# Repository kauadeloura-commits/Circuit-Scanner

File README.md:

# Circuit Scanner

Programa de reconhecimento, revisão e simulação de circuitos eletrônicos fotografados. O aplicativo fica em `project/`.

## Executar no Windows

Na pasta `project`, instale as dependências e abra o programa:

```powershell
python -m venv venv
.\venv\Scripts\python.exe -m pip install -r requirements.txt
.\venv\Scripts\python.exe iniciar_scanner.py
```

Os modelos, referências de reconhecimento, dados ativos de aprendizado e circuitos já salvos foram preservados. A versão principal contém os arquivos usados pelo aplicativo, sem relatórios antigos, auditorias, testes ou cópias de desenvolvimento.

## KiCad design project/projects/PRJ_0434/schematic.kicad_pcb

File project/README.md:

# Circuit Scanner — Etapa 5

Esta versão mantém as Etapas 1–4 e adiciona reconhecimento de componentes
com Ultralytics YOLO.

## O que a Etapa 5 acrescenta

- treinamento do detector;
- modelo salvo em `models/circuit_scanner_yolo.pt`;
- status do modelo na interface;
- reconhecimento dentro de cada projeto;
- classe de cada objeto;
- confiança da previsão;
- bounding box;
- `detections.png`;
- `detections.json`;
- persistência do resultado no SQLite.

## Arquivos principais novos

### backend/recognition.py

Carrega o modelo treinado e converte a saída YOLO para o formato usado
pelo Circuit Scanner.

### scripts/train_yolo.py

Treina o modelo usando `dataset/`.

### scripts/validate_yolo.py

Executa validação do modelo final.

### scripts/detect_image.py

Permite testar o modelo em uma imagem avulsa pelo terminal.

### frontend/yolo.html

Mostra se a biblioteca Ultralytics está instalada e se o modelo final existe.

## Instalação

No CMD do VS Code:

    python -m venv venv
    venv\Scripts\activate
    pip install -r requirements.txt

Backend:

    uvicorn backend.main:app --reload

Frontend, em outro terminal:

    python -m http.server 5500 --directory frontend

Site:

    http://127.0.0.1:5500

## Preparar o dataset

A versão ZIP contém apenas uma pequena amostra para conferência de estrutura.

Antes do treino útil, abra:

    http://127.0.0.1:5500/dataset.html

e gere 150 imagens por classe ou mais.

## Treinar

Em um terceiro terminal:

    venv\Scripts\activate
    python scripts\train_yolo.py --epochs 10

Esse é o teste inicial.

Depois:

    python scripts\train_yolo.py --epochs 50

O arquivo esperado é:

    models/circuit_scanner_yolo.pt

O script usa por padrão `yolo26n.pt` como modelo base e salva o melhor peso
do treinamento com o nome usado pelo Circuit Scanner.

## Detectar

Abra um projeto no site e clique:

    Reconhecer componentes com YOLO

O backend usa a imagem original por padrão. A detecção automática executa o
modelo na imagem colorida e também em escala de cinza. Se a imagem colorida
não retornar componentes, é feita ainda uma tentativa em escala de cinza com
resolução maior. Isso evita a perda observada em fotos com iluminação colorida
e no `processed.png` binarizado.

Para testar uma imagem pelo terminal:

    python scripts\detect_image.py caminho\imagem.jpg

Para auditar classes, labels, distribuição dos dados e modelo ativo:

    python scripts\audit_stage5.py

Resultado na pasta do projeto:

    original.png/jpg
    processed.png
    processing.json
    detections.png
    detections.json

As caixas verdes são previsões estáveis. As caixas laranjas com `?` devem ser
conferidas porque possuem confiança baixa ou conflito entre classes parecidas.

Exemplo de `detections.json`:

    {
      "count": 2,
      "detections": [
        {
          "detection_id": "DET_001",
          "class": "resistor",
          "confidence": 0.91,
          "bbox": {
            "x1": 120,
            "y1": 80,
            "x2": 260,
            "y2": 140
          }
        }
      ]
    }

## Observação importante

O ZIP entrega toda a infraestrutura e o código de treinamento/detecção,
mas não contém um modelo Circuit Scanner já treinado. O peso `.pt` depende
do dataset e precisa ser criado executando o treinamento.

Treinar sem erros não é suficiente para concluir a etapa. A conclusão exige
testar cinco circuitos inéditos com a imagem original e registrar componentes
reais, reconhecidos, trocados e ausentes. Falhas pontuais podem ser corrigidas
na conferência; falhas sistemáticas exigem novas anotações reais.

## Ainda não entra nesta etapa

- OCR de R1, 10k, C1 etc.;
- detecção dos terminais;
- fios;
- junções;
- conectividade;
- ngspice;
- KiCad;
- PCB;
- QR Code.

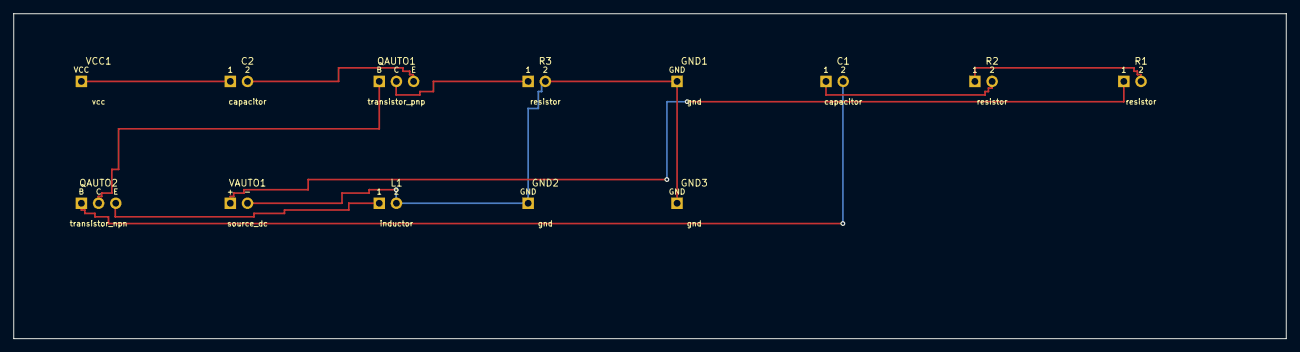
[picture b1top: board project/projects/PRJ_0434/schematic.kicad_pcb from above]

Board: 2 copper layers, 188.0 x 48.0 mm, 13 parts (0 on the bottom side), 10 nets.

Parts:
C1, C2: capacitor; terminal_2
GND1, GND2, GND3: gnd; terminal_1
L1: inductor; terminal_2
QAUTO1: transistor_pnp; terminal_3
QAUTO2: transistor_npn; terminal_3
R1, R2, R3: resistor; terminal_2
VAUTO1: source_dc; terminal_2
VCC1: vcc; terminal_1

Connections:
GND: GND1.1, GND2.1, GND3.1, L1.2, R3.2, VAUTO1.2
NET_1: C2.2, QAUTO1.3
NET_2: QAUTO1.1, QAUTO2.2
NET_5: QAUTO1.2, R3.1
NET_6: R1.2, R2.1
NET_7: C1.1, R2.2
NET_8: C1.2, QAUTO2.1
NET_9: R1.1, VAUTO1.1
NET_13: L1.1, QAUTO2.3
NET_14: C2.1, VCC1.1

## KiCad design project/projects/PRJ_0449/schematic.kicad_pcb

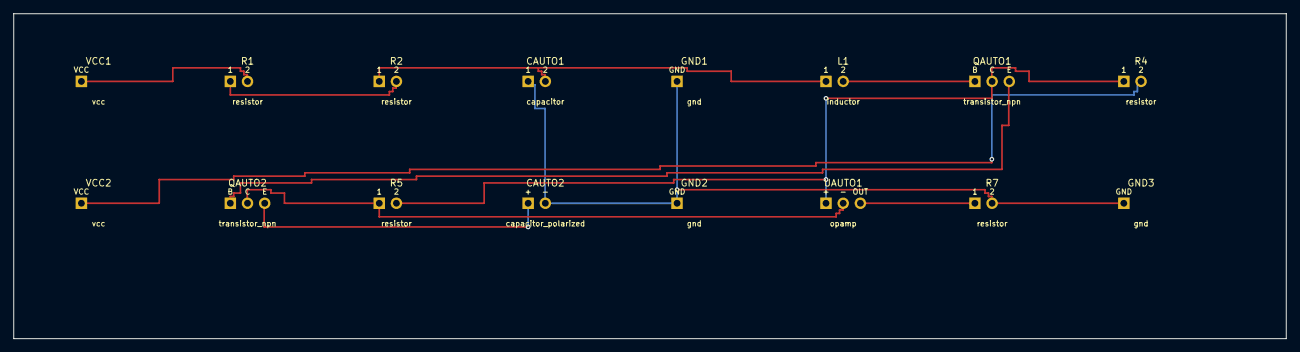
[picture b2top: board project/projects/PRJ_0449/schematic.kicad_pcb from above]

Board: 2 copper layers, 188.0 x 48.0 mm, 16 parts (0 on the bottom side), 11 nets.

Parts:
CAUTO1: capacitor; terminal_2
CAUTO2: capacitor_polarized; terminal_2
GND1, GND2, GND3: gnd; terminal_1
L1: inductor; terminal_2
QAUTO1, QAUTO2: transistor_npn; terminal_3
R1, R2, R4, R5, R7: resistor; terminal_2
UAUTO1: opamp; terminal_3
VCC1, VCC2: vcc; terminal_1

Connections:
GND: CAUTO1.1, CAUTO2.2, GND1.1, GND2.1, GND3.1, R7.2
NET_1: R1.2, VCC1.1
NET_2: R1.1, R2.2
NET_3: CAUTO1.2, L1.1, R2.1
NET_5: L1.2, QAUTO1.1
NET_6: QAUTO1.2, R4.1, R5.2, UAUTO1.1
NET_7: QAUTO1.3, QAUTO2.1
NET_8: R4.2, VCC2.1
NET_9: QAUTO2.2, R5.1, UAUTO1.2
NET_10: CAUTO2.1, QAUTO2.3
NET_11: R7.1, UAUTO1.3

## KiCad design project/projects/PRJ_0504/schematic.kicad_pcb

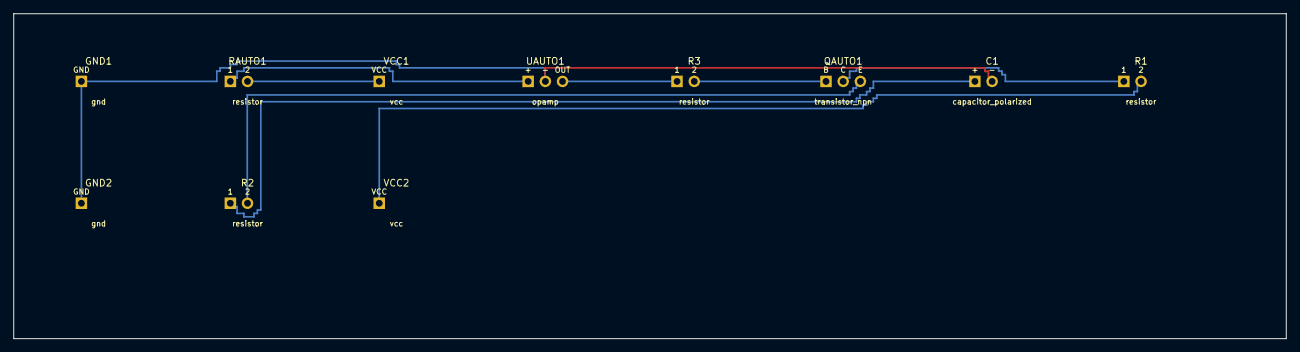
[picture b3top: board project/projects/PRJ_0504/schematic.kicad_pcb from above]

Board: 2 copper layers, 188.0 x 48.0 mm, 11 parts (0 on the bottom side), 9 nets.

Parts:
C1: capacitor_polarized; terminal_2
GND1, GND2: gnd; terminal_1
QAUTO1: transistor_npn; terminal_3
R1, R2, R3: resistor; terminal_2
RAUTO1: resistor; terminal_2
UAUTO1: opamp; terminal_3
VCC1, VCC2: vcc; terminal_1

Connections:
GND: C1.2, GND1.1, GND2.1, UAUTO1.2
NET_2: RAUTO1.1, UAUTO1.1
NET_3: RAUTO1.2, VCC1.1
NET_4: R3.1, UAUTO1.3
NET_5: QAUTO1.1, R3.2
NET_6: QAUTO1.2, R1.1
NET_7: QAUTO1.3, R2.2
NET_8: C1.1, R2.1
NET_9: R1.2, VCC2.1

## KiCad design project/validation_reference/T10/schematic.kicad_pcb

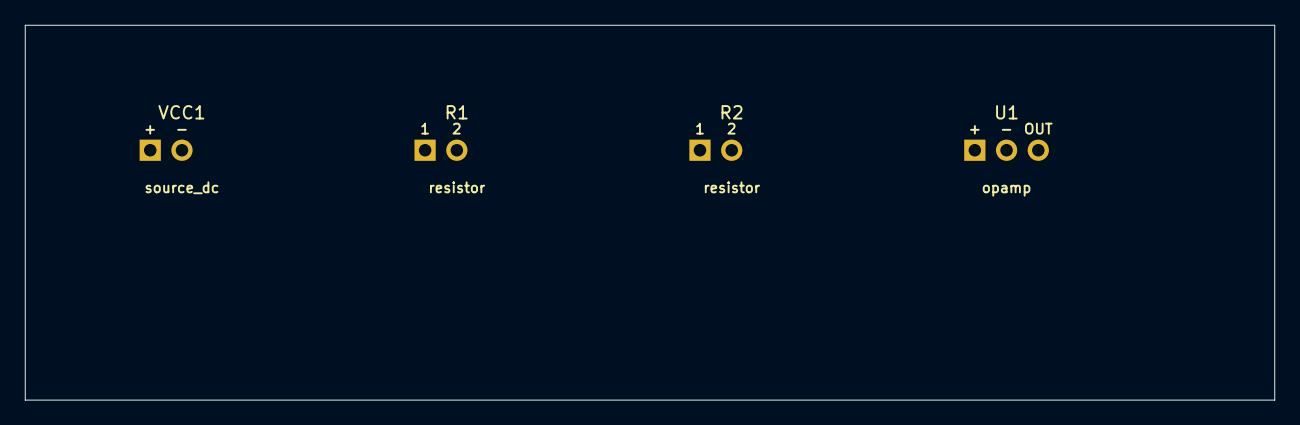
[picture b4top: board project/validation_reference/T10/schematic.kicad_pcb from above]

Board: 2 copper layers, 100.0 x 30.0 mm, 4 parts (0 on the bottom side), 4 nets, no tracks yet.

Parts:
R1, R2: resistor; terminal_2
U1: opamp; terminal_3
VCC1: source_dc; terminal_2

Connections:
BUFFER: U1.2, U1.3
GND: R2.2, VCC1.2
VIN: R1.1, VCC1.1
VOUT: R1.2, R2.1, U1.1

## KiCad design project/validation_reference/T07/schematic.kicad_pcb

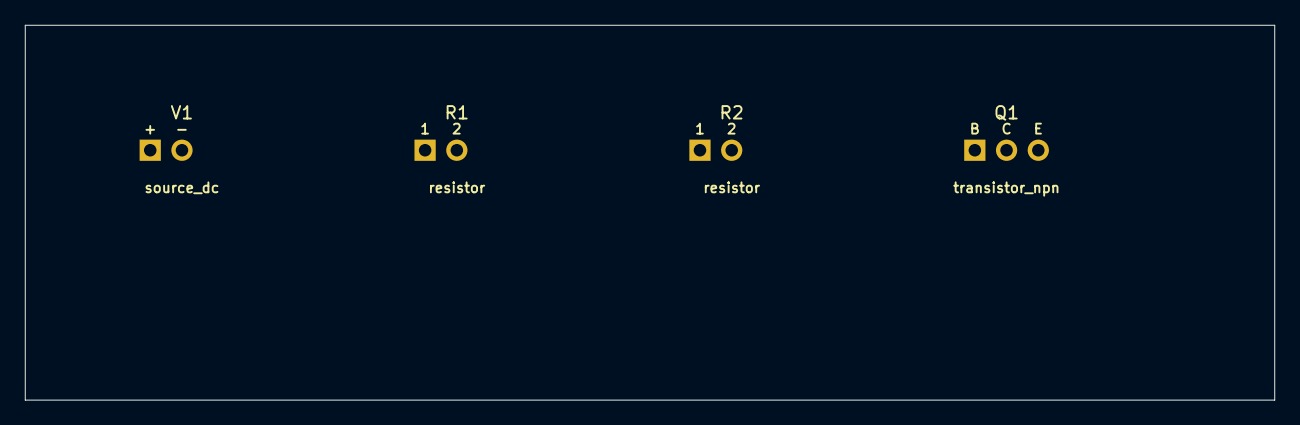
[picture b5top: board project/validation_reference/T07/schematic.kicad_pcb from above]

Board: 2 copper layers, 100.0 x 30.0 mm, 4 parts (0 on the bottom side), 4 nets, no tracks yet.

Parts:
Q1: transistor_npn; terminal_3
R1, R2: resistor; terminal_2
V1: source_dc; terminal_2

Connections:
BASE: Q1.1, R1.2
GND: Q1.3, V1.2
OUT: Q1.2, R2.2
VIN: R1.1, R2.1, V1.1

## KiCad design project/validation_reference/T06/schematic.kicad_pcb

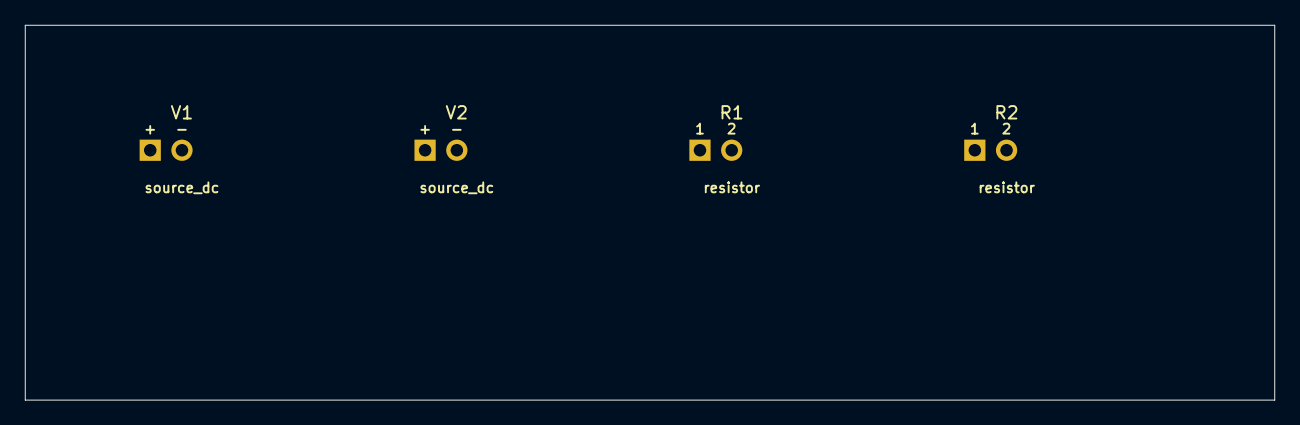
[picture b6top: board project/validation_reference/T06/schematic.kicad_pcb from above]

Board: 2 copper layers, 100.0 x 30.0 mm, 4 parts (0 on the bottom side), 3 nets, no tracks yet.

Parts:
R1, R2: resistor; terminal_2
V1, V2: source_dc; terminal_2

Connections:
BRANCH1: R1.1, V1.1
BRANCH2: R2.1, V2.1
GND: R1.2, R2.2, V1.2, V2.2

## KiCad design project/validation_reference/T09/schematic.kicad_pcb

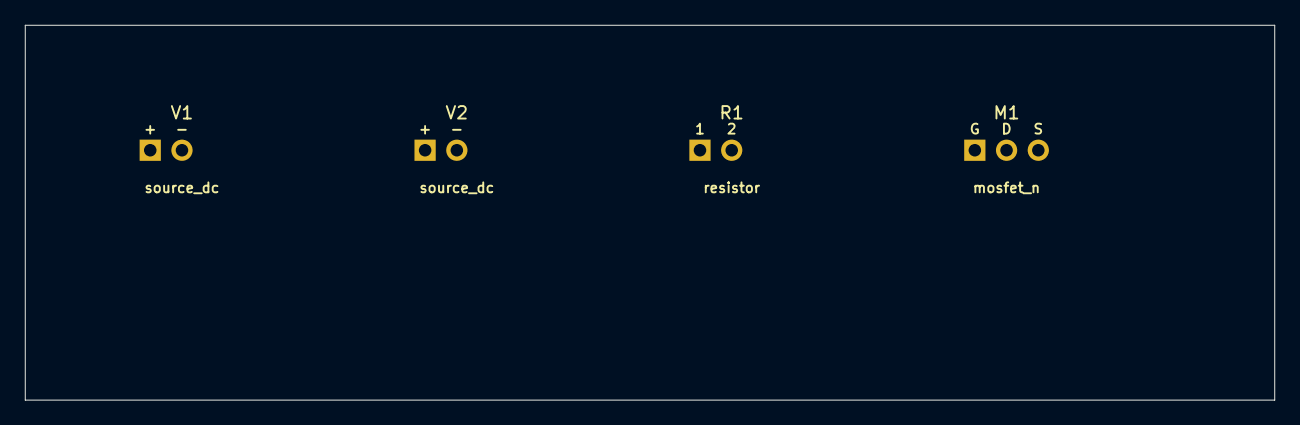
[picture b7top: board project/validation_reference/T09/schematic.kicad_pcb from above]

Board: 2 copper layers, 100.0 x 30.0 mm, 4 parts (0 on the bottom side), 4 nets, no tracks yet.

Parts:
M1: mosfet_n; terminal_3
R1: resistor; terminal_2
V1, V2: source_dc; terminal_2

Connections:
GATE: M1.1, V2.1
GND: M1.3, V1.2, V2.2
OUT: M1.2, R1.2
VIN: R1.1, V1.1

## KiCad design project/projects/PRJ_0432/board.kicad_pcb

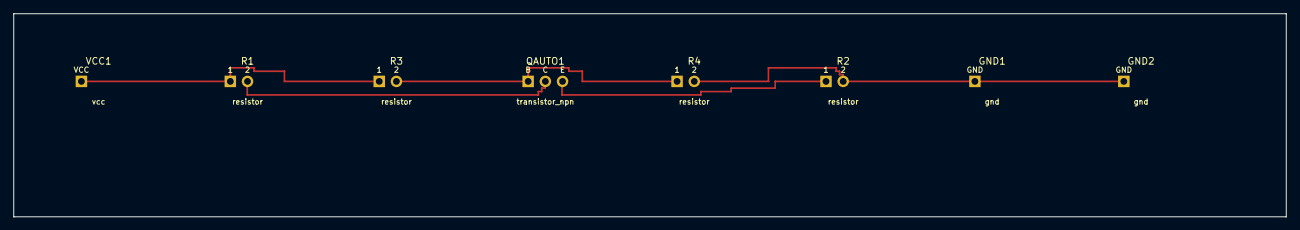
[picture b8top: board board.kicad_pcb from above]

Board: 2 copper layers, 188.0 x 30.0 mm, 8 parts (0 on the bottom side), 5 nets.

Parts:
GND1, GND2: gnd; terminal_1
QAUTO1: transistor_npn; terminal_3
R1, R2, R3, R4: resistor; terminal_2
VCC1: vcc; terminal_1

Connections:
GND: GND1.1, GND2.1, R2.2, R4.2
NET_1: R1.1, R3.1, VCC1.1
NET_2: QAUTO1.2, R1.2
NET_3: QAUTO1.1, R3.2, R4.1
NET_4: QAUTO1.3, R2.1
